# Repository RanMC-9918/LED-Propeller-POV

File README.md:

# LED-Propeller-POV

## Description

This project is a high-speed persistence-of-vision (POV) display that creates images by spinning LED strips on rotating propeller blades. The propellers should be able to rotate at 3,000 RPM and the LEDs are synchronized with the fan's position using a hall effect sensor to create an image in the air. The ESP32 microcontroller should have the bandwidth needed to live stream video to the display in real time.

## PCB

The PCB has components needed to control the LED and motor and an ESP32 to handle communication and LED control. The 12V from the battery is fed into the motor via a motor controller (H-Bridge), then the 12V is stepped down to 5V to power the LEDs and ESP32. The signal coming out of the ESP32 is 3.3V but the LED strip needs 5V so the Bus Buffer converts the signal to 5V for the LED. All pcb traces handling the motors 12V 5A peak are thickened to reduce resistance and heat.

## Criteria

- Must display readable text + graphic
- ≥ 64 columns × 32 rows
- Image jitter < 2° arc at speed
- Image changeable without stopping (Data stream over WiFi)
- Full RGB

## Calculations

### Speed of fan

To determine the ideal RPM of the fan we need the length of persistance of vision for the average person.

https://sky-lights.org/2023/07/24/qa-persistence-of-vision/ reports the persistance of vision to last 10 - 20ms for the average person so I used 10 milliseconds to calculate ideal RPM.

$ RPM = ((1000 / 10) * 60) / 2 = 3000 $

$10$ is length of persistance of vision.

$1000 / 10$ is the RPS, rotations per second.

The $/2$ is because the fan has 2 propellers each giving their own signal to the eye per rotation.

Note: This is ideal RPM and most LED Propeller fan designs use lower RPM for safety, although a flicker might be visible in-person.

### Clock rate of LED Strip

The clock rate of the LED strip/refresh rate limits the speed of the fan and the number of columns.

$ Hz = (RPM / 60) * N $

$Hz$ is refresh rate in Hertz.

$RPM$ is speed of fan

$N$ is number of columns.

Using 3000 RPM and 64 [columns](#criteria):

$ 3200 = (3000 / 60) * 64 $

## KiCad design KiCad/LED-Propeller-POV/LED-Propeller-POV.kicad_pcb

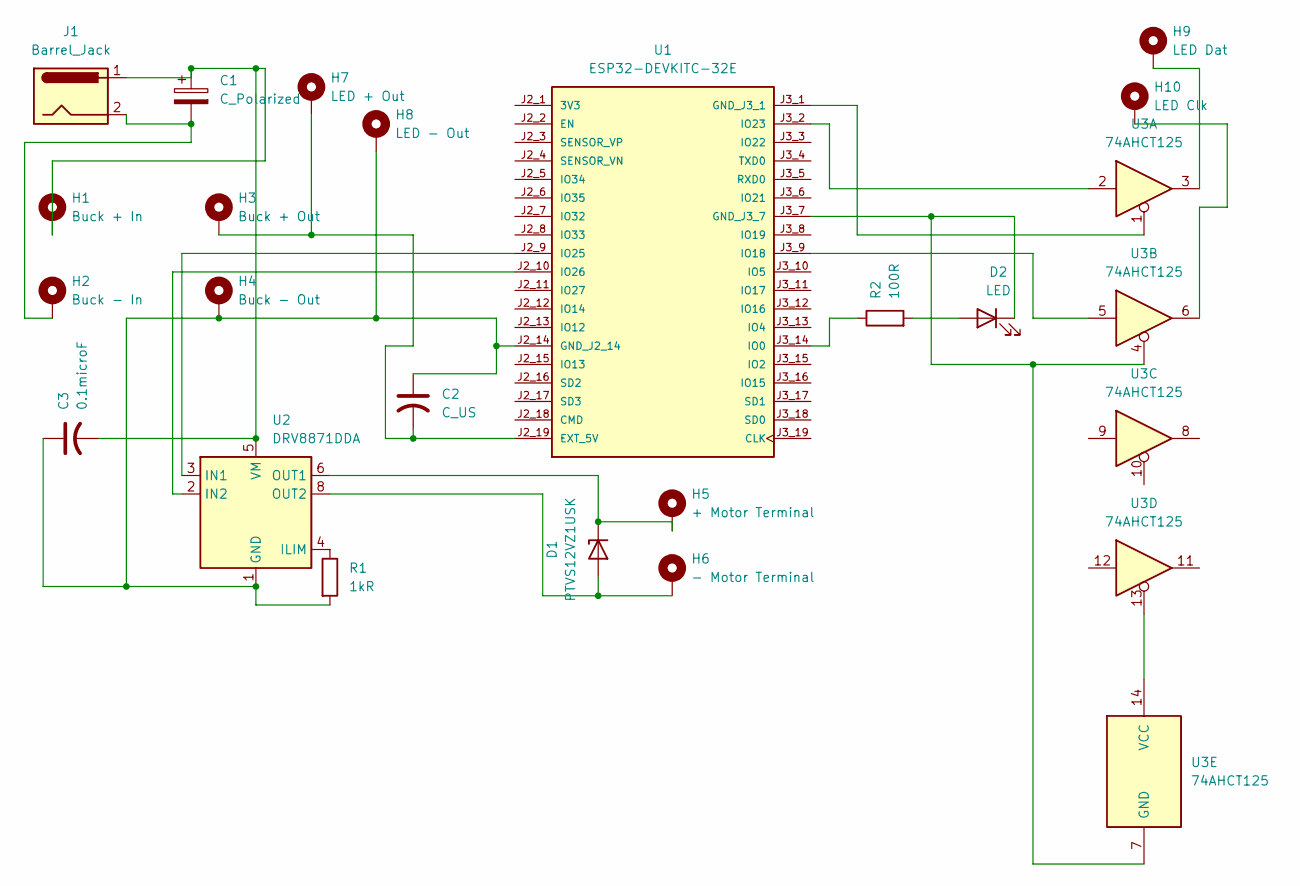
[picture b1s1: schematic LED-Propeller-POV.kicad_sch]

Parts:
C1: C_Polarized; CP_Radial_Tantal_D10.5mm_P5.00mm
C2: C_US; CP_EIA-3216-12_Kemet-S_HandSolder
C3: 0.1microF; CP_EIA-3216-12_Kemet-S_HandSolder
D1: PTVS12VZ1USK; Nexperia_DSN1608-2_1.6x0.8mm
D2: LED; LED_D1.8mm_W1.8mm_H2.4mm_Horizontal_O1.27mm_Z1.6mm
H1: Buck + In; TestPoint_THTPad_4.0x4.0mm_Drill2.0mm
H2: Buck - In; TestPoint_THTPad_4.0x4.0mm_Drill2.0mm
H3: Buck + Out; TestPoint_THTPad_4.0x4.0mm_Drill2.0mm
H4: Buck - Out; TestPoint_THTPad_4.0x4.0mm_Drill2.0mm
H5: + Motor Terminal; TestPoint_THTPad_4.0x4.0mm_Drill2.0mm
H6: - Motor Terminal; TestPoint_THTPad_4.0x4.0mm_Drill2.0mm
H7: LED + Out; TestPoint_THTPad_4.0x4.0mm_Drill2.0mm
H8: LED - Out; TestPoint_THTPad_4.0x4.0mm_Drill2.0mm
H9: LED Dat; TestPoint_THTPad_4.0x4.0mm_Drill2.0mm
H10: LED Clk; TestPoint_THTPad_4.0x4.0mm_Drill2.0mm
J1: Barrel_Jack; BarrelJack_CUI_PJ-063AH_Horizontal_CircularHoles
R1: 1kR; R_0603_1608Metric
R2: 100R; R_Axial_DIN0309_L9.0mm_D3.2mm_P15.24mm_Horizontal
U1: ESP32-DEVKITC-32E; MODULE_ESP32-DEVKITC-32E; PARTREV 1.4
U2: DRV8871DDA; Texas_HTSOP-8-1EP_3.9x4.9mm_P1.27mm_EP2.95x4.9mm_Mask2.4x3.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
U3: 74AHCT125; DIP-14_W7.62mm_Socket_LongPads

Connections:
unnamed: C1.2, H2.1 (1_1), J1.2
unnamed: D1.2 (A), H6.1 (1_1), U2.8 (OUT2)
unnamed: D1.1 (K), H5.1 (1_1), U2.6 (OUT1)
unnamed: D2.2 (A), R2.2
unnamed: D2.1 (K), U1.J3_7 (GND_J3_7), U3.4, U3.7 (GND)
unnamed: H9.1 (1_1), U3.3
unnamed: H10.1 (1_1), U3.6
unnamed: C2.2, H3.1 (1_1), H7.1 (1_1), U1.J2_19 (EXT_5V)
unnamed: C2.1, C3.1, H4.1 (1_1), H8.1 (1_1), R1.2, U1.J2_14 (GND_J2_14), U2.1 (GND), U2.7 (GND), U2.9 (GND)
unnamed: U1.J3_1 (GND_J3_1), U3.1
unnamed: R2.1, U1.J3_14 (IO0)
unnamed: U1.J3_9 (IO18), U3.5
unnamed: U1.J3_2 (IO23), U3.2
unnamed: U1.J2_9 (IO25), U2.3 (IN1)
unnamed: U1.J2_10 (IO26), U2.2 (IN2)
unnamed: R1.1, U2.4 (ILIM)
unnamed: C1.1, C3.2, H1.1 (1_1), J1.1, U2.5 (VM)
unnamed: U3.13, U3.14 (VCC)

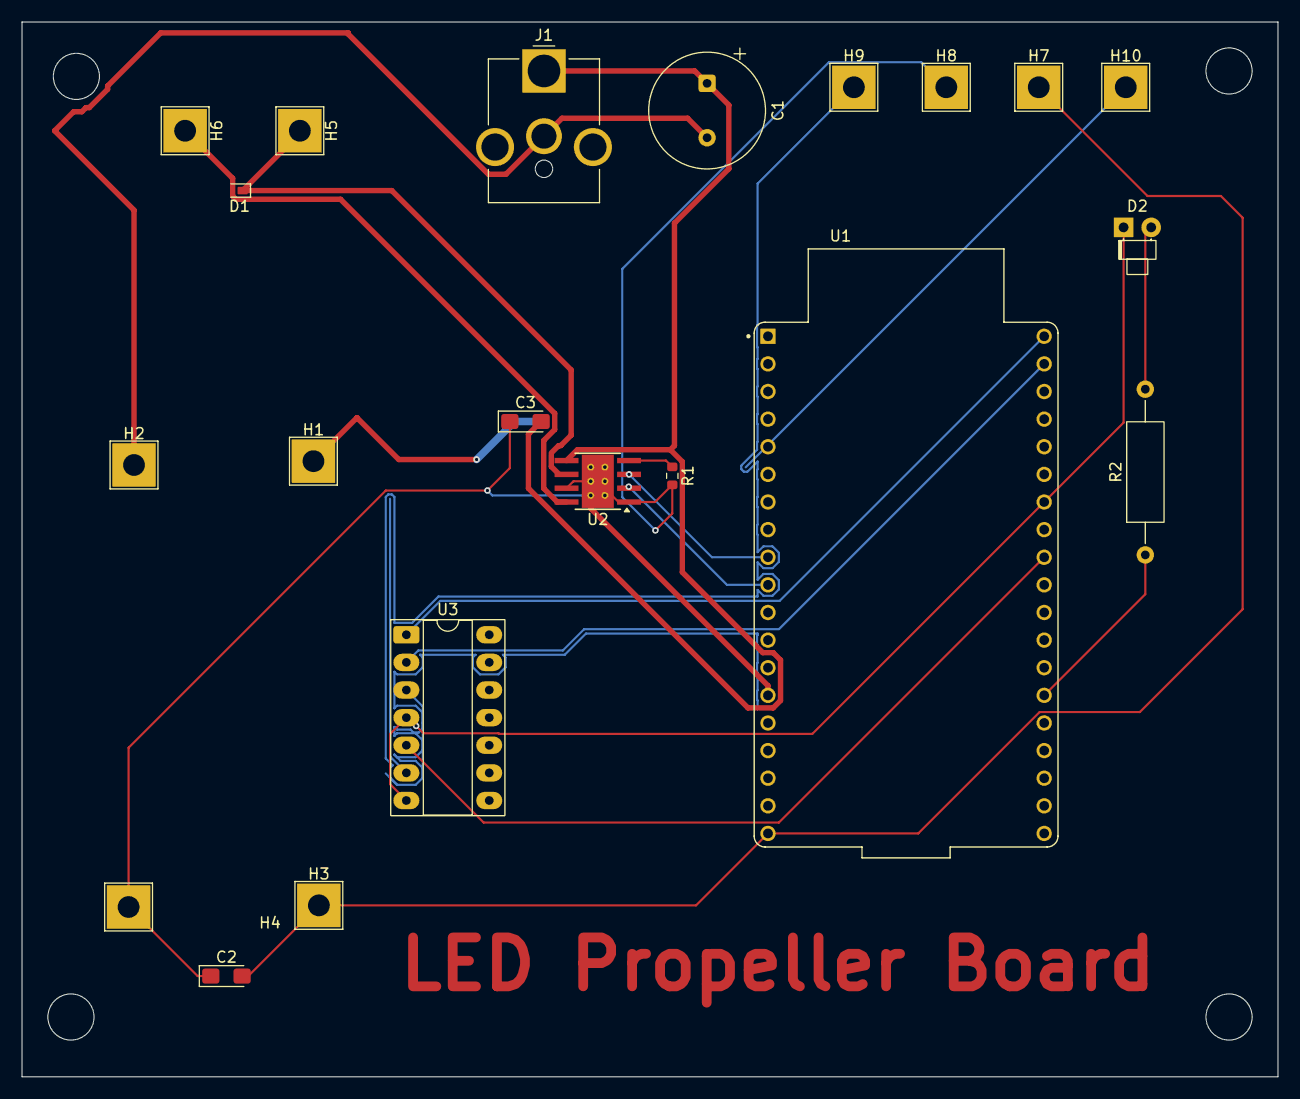
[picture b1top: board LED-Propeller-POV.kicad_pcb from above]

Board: 2 copper layers, 115.5 x 97.0 mm, 21 parts (0 on the bottom side), 18 nets.

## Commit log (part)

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2026-06-19 jun19 update
